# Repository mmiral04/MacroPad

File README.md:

# Introduction
Custom 3x3 MacroPad built with an ESP32. The purpose of the project is to experiment with PCB design and ESP32 programming. The hardware connects via bluetooth to a desktop app designed in Python.

The build is made up of a PCB, a metal frame and 9 MX switches. The electronic components needed are>

* ESP32 DevKit V1 board
* 1 resistor
* 1 LED
* 1 sideways 3-pin switch
* 1 switch
* 1 9V battery

# File structure

* The C code for the ESP32 is located inside the folder "EspCode". Upload this to ESP32 using Arduino IDE.
* The KiCad PCB design files are located inside the folder "KicadFiles". They have been developed in KiCad 9.
* The final PCB schematics, .step file for the metal frame, FreeCad project file for the metal frame and other files used in the design are located in the folder "DesignFiles".
* The code for the desktop app is located in the folder "Python" and "UI".

# Project build

The python app was built into an executable to execute on Windows startup using pyinstaller with the following command:

```

pyinstaller -F --noconsole --icon icon.ico Python\\main.py

```

The final build should look like:

# Usage

The desktop app has a GUI to connect to the macro pad via bluetooth and configure the macros. Currently the macros can be of three types:

* Keyboard shortcut (keys separated by +, e.g. "Ctrl + Shift + Esc" to open the Task Manager)
* Launch an application
* Launch a python script

All of the options can be customized with an icon or name.

The configuration of the macros is stored in the file "Python/config.json". When the application is closed it runs in the background and appears in the icon tray, where it can be fully exited.

The connection to the board via bluetooth has the MAC address of the board hardcoded in the python file "Python/main.py" and must be changed to the actual MAC address of the ESP32.

# Bugs and limitations

There are some limitations and bugs in the design:

* The 9V battery is not a viable power source as it drains the battery quickly. I am currently using the macro pad connected directly to the PC with USB.
* Connecting the macro pad via USB should not use bluetooth to connect, it would be better the use serial communication.
* If connecting the macro pad via USB with the PC, when another device is connected to the same computer via USB windows refreshes all USB devices and powers off the macro pad, leading to connection issues.

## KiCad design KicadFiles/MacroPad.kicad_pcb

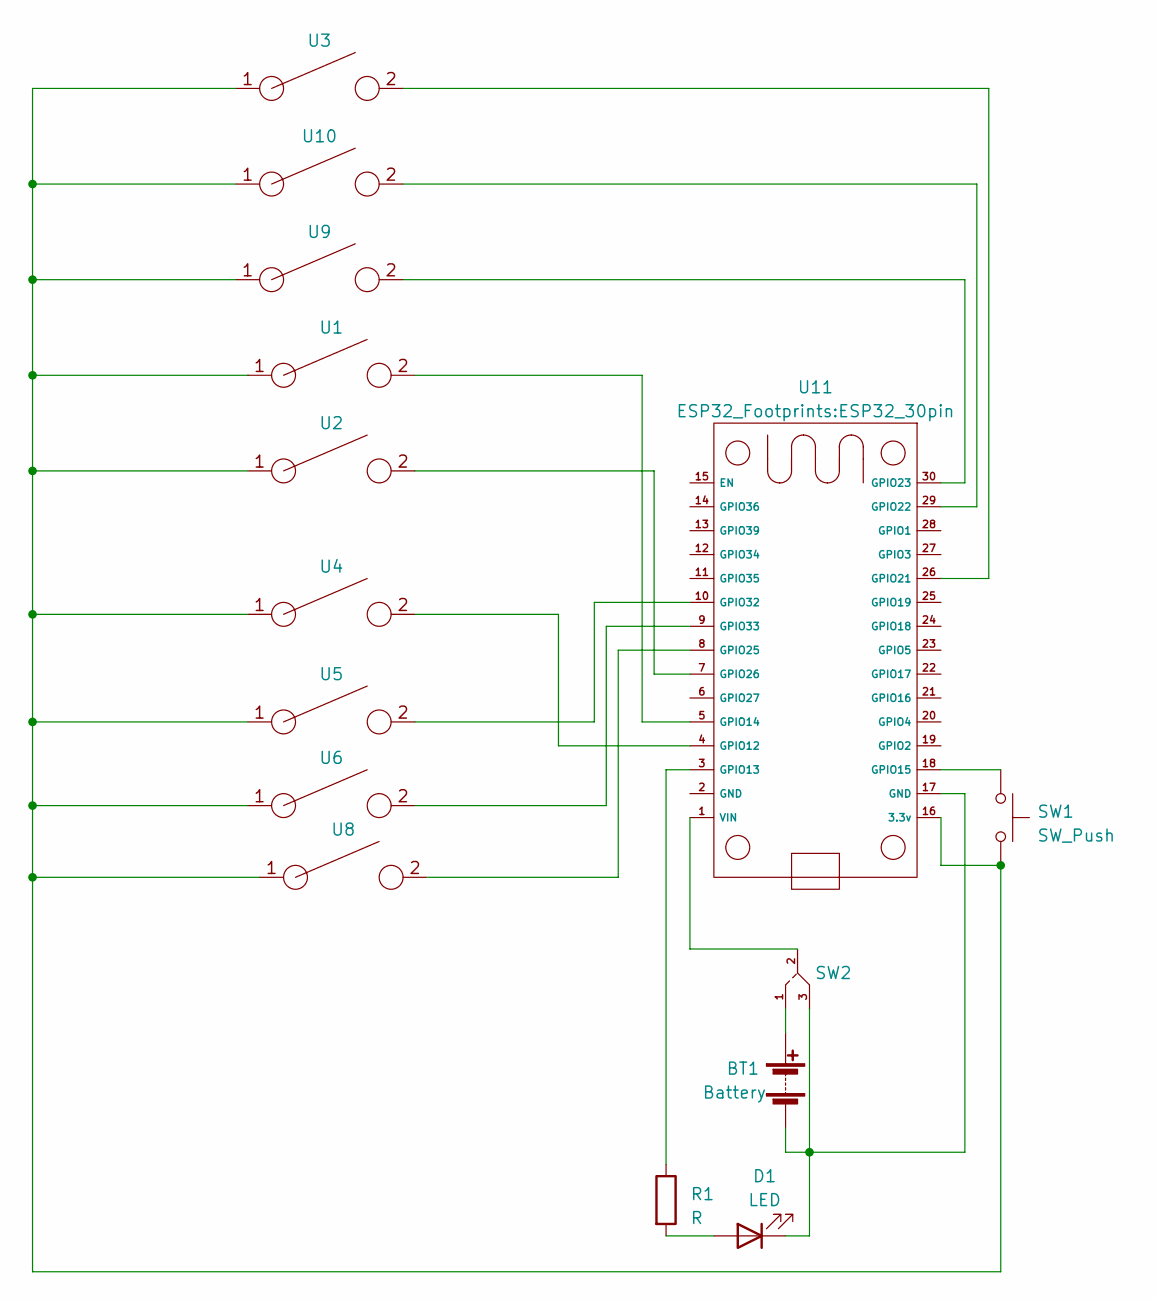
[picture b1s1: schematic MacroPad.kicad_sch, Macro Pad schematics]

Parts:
BT1: Battery; Battery holder
D1: LED; LED_holes
R1: R; Resistor_holes
SW1: SW_Push; SW_PUSH_6mm_H5mm
SW2: Switch conmutador
U1, U2, U3, U4, U5, U6, U8, U9, U10: SW_Cherry_MX_1.00u_PCB
U11: ESP32_30pin

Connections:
unnamed: BT1.1 (+), SW2.1
unnamed: BT1.2 (-), D1.1 (K), SW2.3, U11.17 (GND)
unnamed: D1.2 (A), R1.2
unnamed: SW1.2, U1.1, U2.1, U3.1, U4.1, U5.1, U6.1, U8.1, U9.1, U10.1, U11.16 (3.3v)
unnamed: U4.2, U11.4 (GPIO12)
unnamed: R1.1, U11.3 (GPIO13)
unnamed: U1.2, U11.5 (GPIO14)
unnamed: SW1.1, U11.18 (GPIO15)
unnamed: U3.2, U11.26 (GPIO21)
unnamed: U10.2, U11.29 (GPIO22)
unnamed: U9.2, U11.30 (GPIO23)
unnamed: U8.2, U11.8 (GPIO25)
unnamed: U2.2, U11.7 (GPIO26)
unnamed: U5.2, U11.10 (GPIO32)
unnamed: U6.2, U11.9 (GPIO33)
unnamed: SW2.2, U11.1 (VIN)

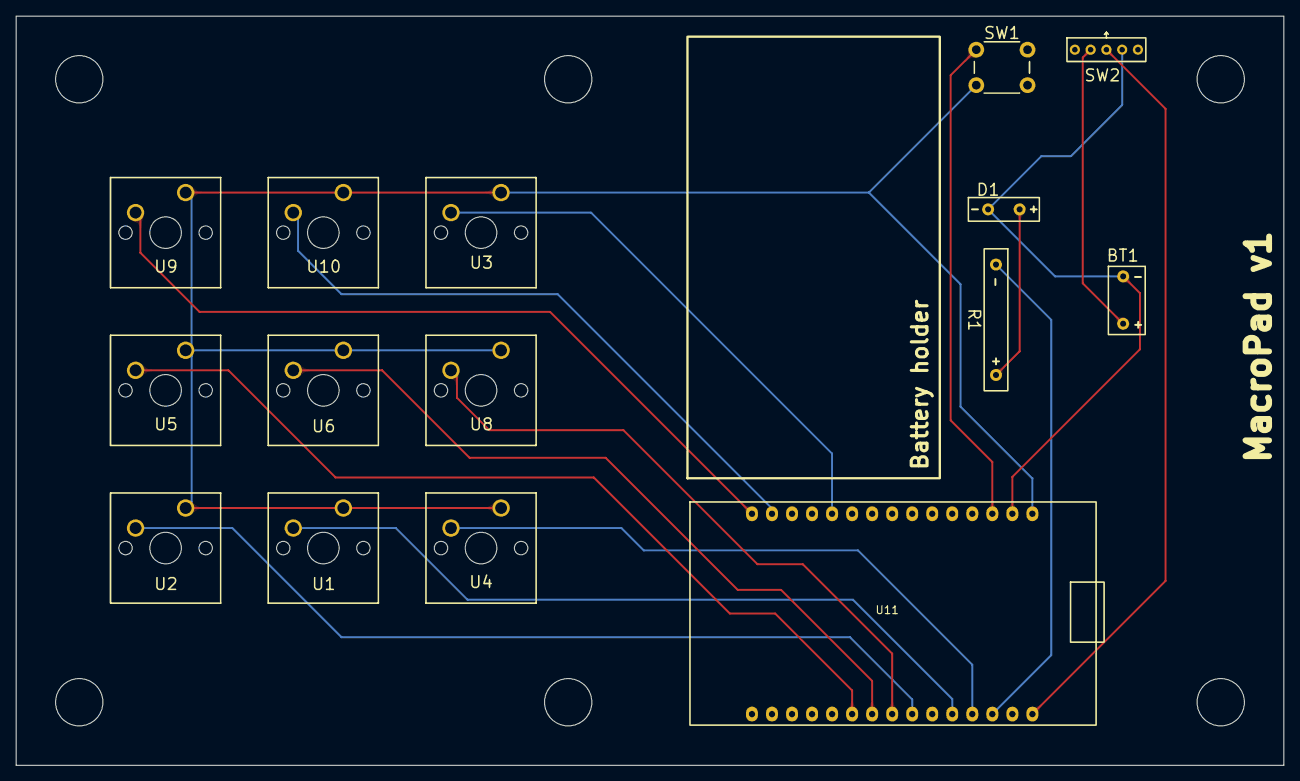
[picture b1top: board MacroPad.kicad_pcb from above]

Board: 2 copper layers, 160.8 x 95.0 mm, 15 parts (0 on the bottom side), 16 nets.

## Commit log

2025-11-19 Init
2025-11-19 Create LICENSE
